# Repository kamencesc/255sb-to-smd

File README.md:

# 255SB Toggle Switch to a SMD Toggle Switch
If you are a kind of $%&# head and you has used a lot of 255SB Toggle Switch in your projects, just to realese when the first batch of 50 PCBs are in yout hand and... that the 255SB does't use a standard DIP (0.1" 2.54mm distance between pins), but there's no 255SB anywhere! Ebay, Aliexpres, LCSC... What can I do?

Just use one of this 3 adapters.

1. The first one is a simple adapter that uses a SMT male pin header and a SMT SPDT Toggle switch.
2. The second one is the first one but is double, same size as 2x255SB perfectly joined.
3. The third one a vertical hone, use a 90º SMT male pinheader and a SMT SPDT Toggle switch at 90º

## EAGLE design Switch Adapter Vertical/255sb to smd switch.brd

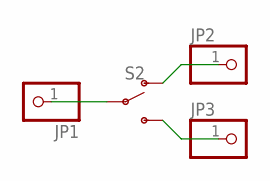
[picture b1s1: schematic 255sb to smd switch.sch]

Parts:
JP1, JP2, JP3: PINHD-1X01_2.54-SMD-90°; 1X01SMD/90
S2: SWITCH-SPDT-SMD-RIGHT-ANGLE; SWITCH_SPST_SMD_A

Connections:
unnamed: JP2.1, S2.1 (O)
unnamed: JP3.1, S2.3 (S)
unnamed: JP1.1, S2.2

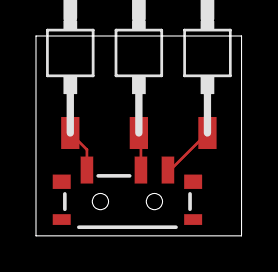
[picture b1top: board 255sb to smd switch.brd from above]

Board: 2 copper layers, 11.4 x 11.1 mm, 4 parts (0 on the bottom side), 3 nets.

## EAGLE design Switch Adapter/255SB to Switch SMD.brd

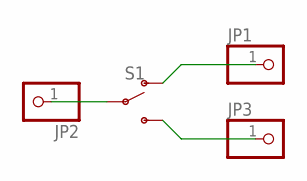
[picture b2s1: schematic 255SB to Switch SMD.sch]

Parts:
JP1, JP2, JP3: PINHD-1X01_2.54-SMD; 1X01SMD
S1: SWITCH-SPDT-SMD-AYZ0202; SWITCH_DPDT_SMD_AYZ0202

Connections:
unnamed: JP2.1, S1.2
unnamed: JP1.1, S1.1 (O)
unnamed: JP3.1, S1.3 (S)

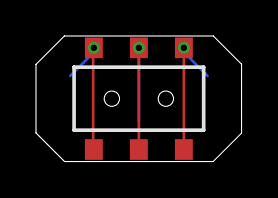
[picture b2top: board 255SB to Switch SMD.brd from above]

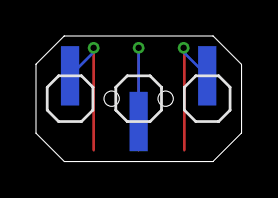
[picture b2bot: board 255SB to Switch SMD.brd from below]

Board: 2 copper layers, 11.4 x 7.0 mm, 4 parts (3 on the bottom side), 3 nets.

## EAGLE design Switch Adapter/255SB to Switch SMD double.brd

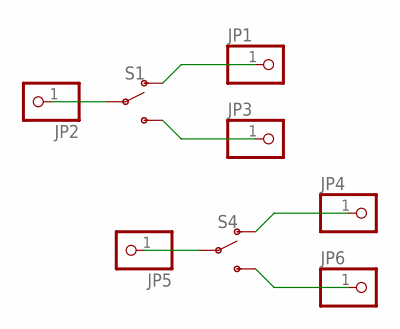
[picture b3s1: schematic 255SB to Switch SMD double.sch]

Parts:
JP1, JP2, JP3, JP4, JP5, JP6: PINHD-1X01_2.54-SMD; 1X01SMD
S1, S4: SWITCH-SPDT-SMD-AYZ0202; SWITCH_DPDT_SMD_AYZ0202

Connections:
unnamed: JP2.1, S1.2
unnamed: JP1.1, S1.1 (O)
unnamed: JP3.1, S1.3 (S)
unnamed: JP5.1, S4.2
unnamed: JP4.1, S4.1 (O)
unnamed: JP6.1, S4.3 (S)

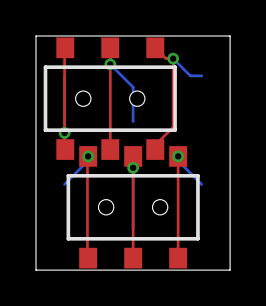
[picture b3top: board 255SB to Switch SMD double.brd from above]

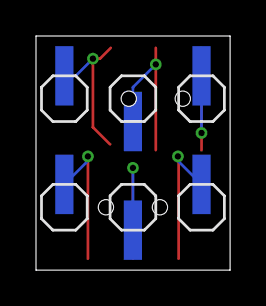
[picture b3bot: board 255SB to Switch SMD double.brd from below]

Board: 2 copper layers, 10.8 x 13.0 mm, 8 parts (6 on the bottom side), 6 nets.

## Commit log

2019-05-28 Add files via upload
    files files files...

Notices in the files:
parts and their libraries:
SparkFun-Switches: Licensing: Creative Commons ShareAlike 4.0 International - https://creativecommons.org/licenses/by-sa/4.0
